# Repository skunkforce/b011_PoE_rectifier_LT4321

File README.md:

# edgy_board number b011
This design is part of the [edgy board project](https://github.com/skunkforce/edgy_boards). It provides a highly power efficient bridge rectifier for PoE applications. 

# getting started
This repository uses submodules. After cloning use the command 

```$ git submodule update --init --recursive```

to pull the submodules before opening the project with kicad. 

# Tests
Tests can be found in [TESTS.md](TESTS.md)

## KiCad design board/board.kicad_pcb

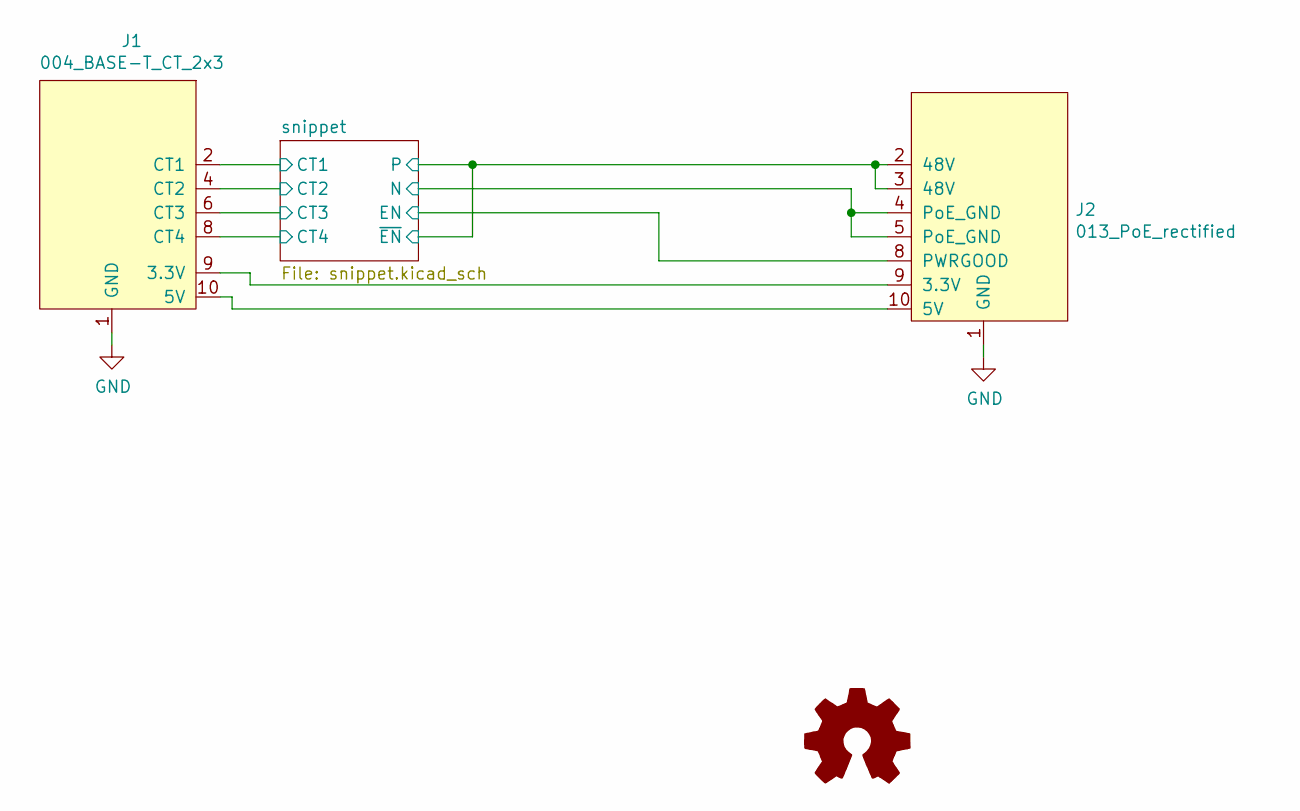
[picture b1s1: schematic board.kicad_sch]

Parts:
J1: 004_BASE-T_CT_2x3; on_edge_2x05_device
J2: 013_PoE_rectified; on_edge_2x05_host
LOGO1: Logo_Open_Hardware_Small; OSHW-Logo2_9.8x8mm_SilkScreen

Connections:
/snippet/CT_12: J1.2 (CT1); also elsewhere on the board
/snippet/CT_36: J1.4 (CT2); also elsewhere on the board
/snippet/CT_45: J1.6 (CT3); also elsewhere on the board
/snippet/CT_78: J1.8 (CT4); also elsewhere on the board
/snippet/EN: J2.8 (PWRGOOD); also elsewhere on the board
/snippet/VPORTN: J2.4 (PoE_GND), J2.5 (PoE_GND); also elsewhere on the board
/snippet/VPORTP: J2.2 (48V), J2.3 (48V); also elsewhere on the board
GND: J1.1 (GND), J2.1 (GND)
unnamed: J1.9 (3.3V), J2.9 (3.3V)
unnamed: J1.10 (5V), J2.10 (5V)

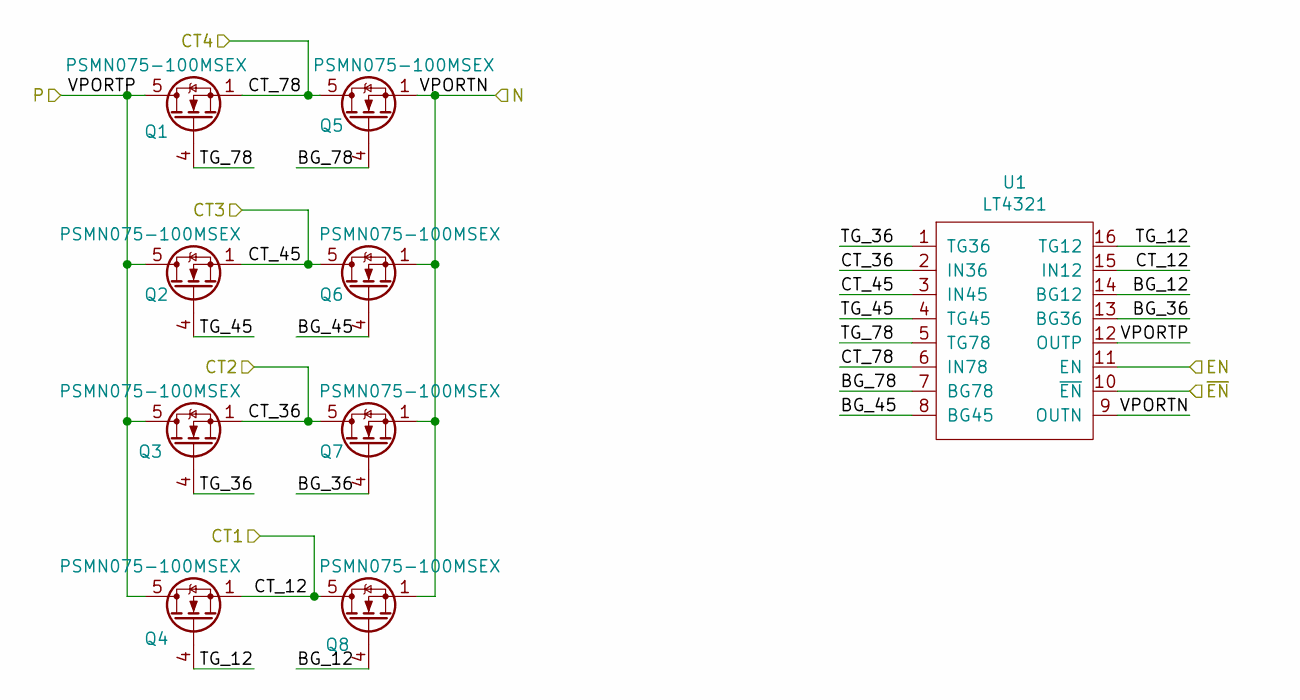
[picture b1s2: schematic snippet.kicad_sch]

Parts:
Q1, Q2, Q3, Q4, Q5, Q6, Q7, Q8: PSMN075-100MSEX; LFPAK33; MPN PSMN075-100MSEX
U1: LT4321; WQFN-16-1EP_4x4mm_P0.5mm_EP2.6x2.6mm; MPN LT4321IUF#PBF; Digi-Key_PN LT4321IUF#PBF-ND

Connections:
/snippet/BG_12: Q8.4 (G), U1.14 (BG12)
/snippet/BG_36: Q7.4 (G), U1.13 (BG36)
/snippet/BG_45: Q6.4 (G), U1.8 (BG45)
/snippet/BG_78: Q5.4 (G), U1.7 (BG78)
/snippet/CT_12: Q4.1 (S), Q4.2 (S), Q4.3 (S), Q8.5 (D), U1.15 (IN12); also elsewhere on the board
/snippet/CT_36: Q3.1 (S), Q3.2 (S), Q3.3 (S), Q7.5 (D), U1.2 (IN36); also elsewhere on the board
/snippet/CT_45: Q2.1 (S), Q2.2 (S), Q2.3 (S), Q6.5 (D), U1.3 (IN45); also elsewhere on the board
/snippet/CT_78: Q1.1 (S), Q1.2 (S), Q1.3 (S), Q5.5 (D), U1.6 (IN78); also elsewhere on the board
/snippet/EN: U1.11 (EN); also elsewhere on the board
/snippet/TG_12: Q4.4 (G), U1.16 (TG12)
/snippet/TG_36: Q3.4 (G), U1.1 (TG36)
/snippet/TG_45: Q2.4 (G), U1.4 (TG45)
/snippet/TG_78: Q1.4 (G), U1.5 (TG78)
/snippet/VPORTN: Q5.1 (S), Q5.2 (S), Q5.3 (S), Q6.1 (S), Q6.2 (S), Q6.3 (S), Q7.1 (S), Q7.2 (S), Q7.3 (S), Q8.1 (S), Q8.2 (S), Q8.3 (S), U1.9 (OUTN), U1.17 (EP); also elsewhere on the board
/snippet/VPORTP: Q1.5 (D), Q2.5 (D), Q3.5 (D), Q4.5 (D), U1.10 (~EN), U1.12 (OUTP); also elsewhere on the board

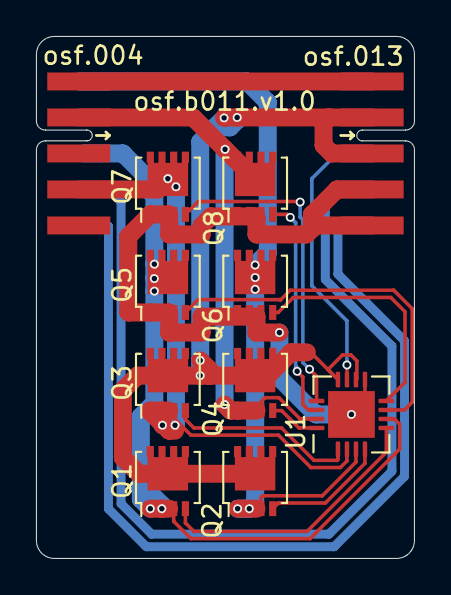
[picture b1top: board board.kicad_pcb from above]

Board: 2 copper layers, 21.0 x 29.0 mm, 12 parts (1 on the bottom side), 18 nets.

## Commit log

2023-02-24 improved description
2023-02-24 imported legacy version
2023-05-13 updated connectors, changed mosfets and added enable resistors
2023-05-14 added enable input from downstream
